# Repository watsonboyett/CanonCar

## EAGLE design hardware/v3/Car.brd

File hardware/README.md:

# Revision History

## v3A

- Added reverse polarity protection diode to power input (7V-35V input range?)

## Future Changes
* Change MCU to ATSAMD51J19A
  * Make it pin compatible with Metro M4 or Feather M4 boards, so Arduino IDE can be used easily
* Select better motor driver
  * TI DRV8848 - PWM interface, smaller, higher current output
  * Allegro A4970 - Same functionality as MTS62C19A, different pinout
  * Microchip MTS2916A - Same functionality as MTS62C19A, different pinout (same as A4970)
  * Toshiba TB6552 - Similar functionality as MTS62C19A
* Replace RFM12 module with RFM69 (RFM12 is obsolete now)
* Replace linear power regulators with buck converters
  * Is 5V supply actually needed?
  * Consider AOZ128x ICs
* Replace Mini-USB with Micro-USB connector
* Use SMT jack for DC plug (PJ-002AH-SMT)
* Use SMT headers for all external pin connectors
  * JST-PH connectors?
* Add support for battery charging circuit
  * NiMH on RC car side
  * LiPo on controller side

## Wiring Notes 

- all white lines connected to ground
- S-F (fire): orange, white
- S-R (right): purple, white
- S-L (left): green, white
- S-D (down): blue, white
- S-U (up): brown, white

- M3-F (fire): orange, red (red connected to +5V)
- M2-L/R (left/right): yellow, red
- M3-U/D (up/down): brown, red

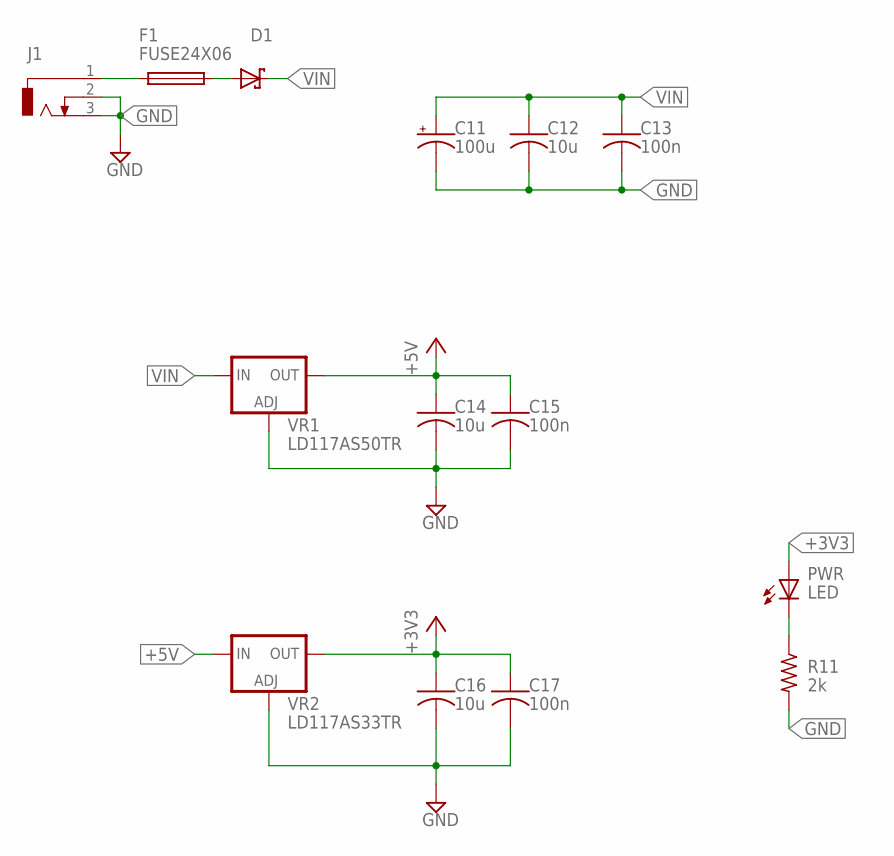
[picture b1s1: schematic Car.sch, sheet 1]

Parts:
C11: 100u; PANASONIC_C
C12, C14, C16: 10u; C1206
C13, C15, C17: 100n; C0805
D1: SCHOTTKY-DIODESMA; SMA
F1: FUSE24X06; 2SMD-24X06
J1: DCJ0303
PWR: LED; CHIP-LED0805
R11: 2k; R0805
VR1: LD117AS50TR; SOT223
VR2: LD117AS33TR; SOT223

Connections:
+3V3: C16.1, C17.1, PWR.A, VR2.2 (OUT), VR2.4 (OUT); also elsewhere on the board
+5V: C14.1, C15.1, VR1.2 (OUT), VR1.4 (OUT), VR2.3 (IN); also elsewhere on the board
GND: C11.-, C12.2, C13.2, C14.2, C15.2, C16.2, C17.2, J1.2, J1.3, R11.2, VR1.1 (ADJ), VR2.1 (ADJ); also elsewhere on the board
unnamed: D1.A, F1.P$2 (2)
unnamed: PWR.C, R11.1
VIN: C11.+, C12.1, C13.1, D1.C, VR1.3 (IN); also elsewhere on the board
VIN_PRF: F1.P$1 (1), J1.1

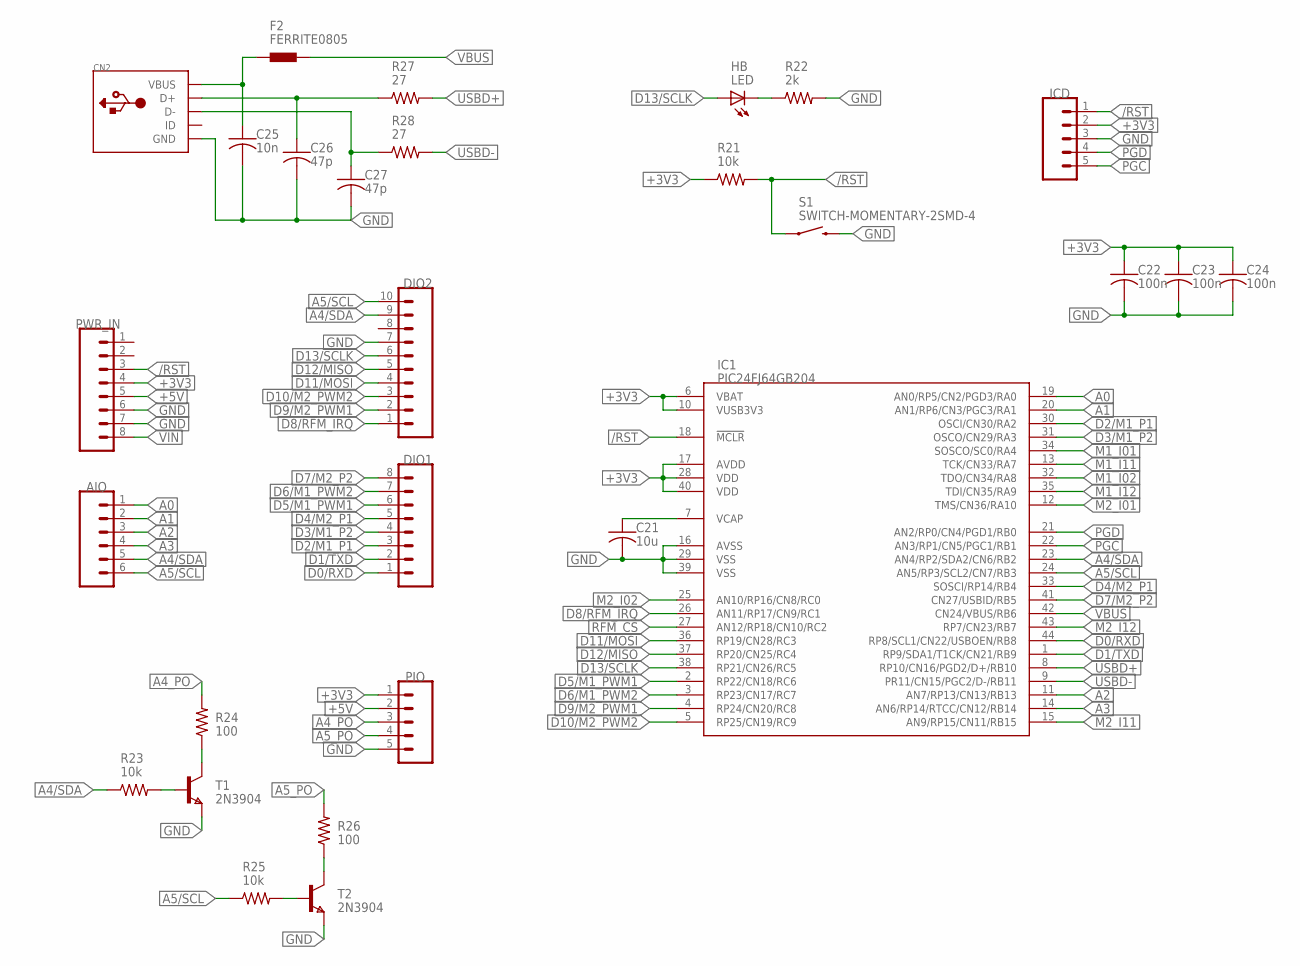
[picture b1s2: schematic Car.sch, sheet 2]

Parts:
AIO: M06LOCK; 1X06_LOCK
C21: 10u; C1206
C22, C23, C24: 100n; C0805
C25: 10n; C0805
C26, C27: 47p; C0805
CN2: USBMINIB; USB-MINIB
DIO1: M08LOCK; 1X08_LOCK
DIO2: M10LOCK; 1X10_LOCK
F2: FERRITE0805; 0805
HB: LED; CHIP-LED0805
IC1: PIC24FJ64GB204; TQFP44
ICD: M05LOCK; 1X05_LOCK
PIO: M05LOCK; 1X05_LOCK
PWR_IN: M08LOCK; 1X08_LOCK
R21, R23, R25: 10k; R0805
R22: 2k; R0805
R24, R26: 100; R0805
R27, R28: 27; R0805
S1: SWITCH-MOMENTARY-2SMD-4; TACTILE_SWITCH_TALL
T1, T2: 2N3904; SOT-23

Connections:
+3V3: C22.1, C23.1, C24.1, IC1.6 (VBAT), IC1.10 (VUSB3V3), IC1.17 (AVDD), IC1.28 (VDD), IC1.40 (VDD), ICD.2, PIO.1, PWR_IN.4, R21.1; also elsewhere on the board
+5V: PIO.2, PWR_IN.5; also elsewhere on the board
/RST: IC1.18 (!MCLR), ICD.1, PWR_IN.3, R21.2, S1.A2 (1); also elsewhere on the board
A0: AIO.1, IC1.19 (AN0/RP5/CN2/PGD3/RA0)
A1: AIO.2, IC1.20 (AN1/RP6/CN3/PGC3/RA1)
A2: AIO.3, IC1.11 (AN7/RP13/CN13/RB13)
A3: AIO.4, IC1.14 (AN6/RP14/RTCC/CN12/RB14)
A4/SDA: AIO.5, DIO2.9, IC1.23 (AN4/RP2/SDA2/CN6/RB2), R23.1
A4_PO: PIO.3, R24.2
A5/SCL: AIO.6, DIO2.10, IC1.24 (AN5/RP3/SCL2/CN7/RB3), R25.1
A5_PO: PIO.4, R26.2
D0/RXD: DIO1.1, IC1.44 (RP8/SCL1/CN22/USBOEN/RB8)
D1/TXD: DIO1.2, IC1.1 (RP9/SDA1/T1CK/CN21/RB9)
D2/M1_P1: DIO1.3, IC1.30 (OSCI/CN30/RA2); also elsewhere on the board
D3/M1_P2: DIO1.4, IC1.31 (OSCO/CN29/RA3); also elsewhere on the board
D4/M2_P1: DIO1.5, IC1.33 (SOSCI/RP14/RB4); also elsewhere on the board
D5/M1_PWM1: DIO1.6, IC1.2 (RP22/CN18/RC6); also elsewhere on the board
D6/M1_PWM2: DIO1.7, IC1.3 (RP23/CN17/RC7); also elsewhere on the board
D7/M2_P2: DIO1.8, IC1.41 (CN27/USBID/RB5); also elsewhere on the board
D8/RFM_IRQ: DIO2.1, IC1.26 (AN11/RP17/CN9/RC1); also elsewhere on the board
D9/M2_PWM1: DIO2.2, IC1.4 (RP24/CN20/RC8); also elsewhere on the board
D10/M2_PWM2: DIO2.3, IC1.5 (RP25/CN19/RC9); also elsewhere on the board
D11/MOSI: DIO2.4, IC1.36 (RP19/CN28/RC3); also elsewhere on the board
D12/MISO: DIO2.5, IC1.37 (RP20/CN25/RC4); also elsewhere on the board
D13/SCLK: DIO2.6, HB.A, IC1.38 (RP21/CN26/RC5); also elsewhere on the board
GND: C21.2, C22.2, C23.2, C24.2, C25.2, C26.2, C27.2, CN2.GND, DIO2.7, IC1.16 (AVSS), IC1.29 (VSS), IC1.39 (VSS), ICD.3, PIO.5, PWR_IN.6, PWR_IN.7, R22.2, S1.B2 (2), T1.2 (E), T2.2 (E); also elsewhere on the board
M1_I01: IC1.34 (SOSCO/SC0/RA4); also elsewhere on the board
M1_I02: IC1.32 (TDO/CN34/RA8); also elsewhere on the board
M1_I11: IC1.13 (TCK/CN33/RA7); also elsewhere on the board
M1_I12: IC1.35 (TDI/CN35/RA9); also elsewhere on the board
M2_I01: IC1.12 (TMS/CN36/RA10); also elsewhere on the board
M2_I02: IC1.25 (AN10/RP16/CN8/RC0); also elsewhere on the board
M2_I11: IC1.15 (AN9/RP15/CN11/RB15); also elsewhere on the board
M2_I12: IC1.43 (RP7/CN23/RB7); also elsewhere on the board
unnamed: R24.1, T1.1 (C)
unnamed: R26.1, T2.1 (C)
unnamed: R23.2, T1.3 (B)
unnamed: R25.2, T2.3 (B)
unnamed: C26.1, CN2.D+, R27.1
unnamed: C27.1, CN2.D-, R28.1
unnamed: C21.1, IC1.7 (VCAP)
unnamed: HB.C, R22.1
PGC: IC1.22 (AN3/RP1/CN5/PGC1/RB1), ICD.5
PGD: IC1.21 (AN2/RP0/CN4/PGD1/RB0), ICD.4
RFM_CS: IC1.27 (AN12/RP18/CN10/RC2); also elsewhere on the board
USBD+: IC1.8 (RP10/CN16/PGD2/D+/RB10), R27.2
USBD-: IC1.9 (PR11/CN15/PGC2/D-/RB11), R28.2
VBUS: F2.2, IC1.42 (CN24/VBUS/RB6)
VBUS-PRF: C25.1, CN2.VBUS, F2.1
VIN: PWR_IN.8; also elsewhere on the board

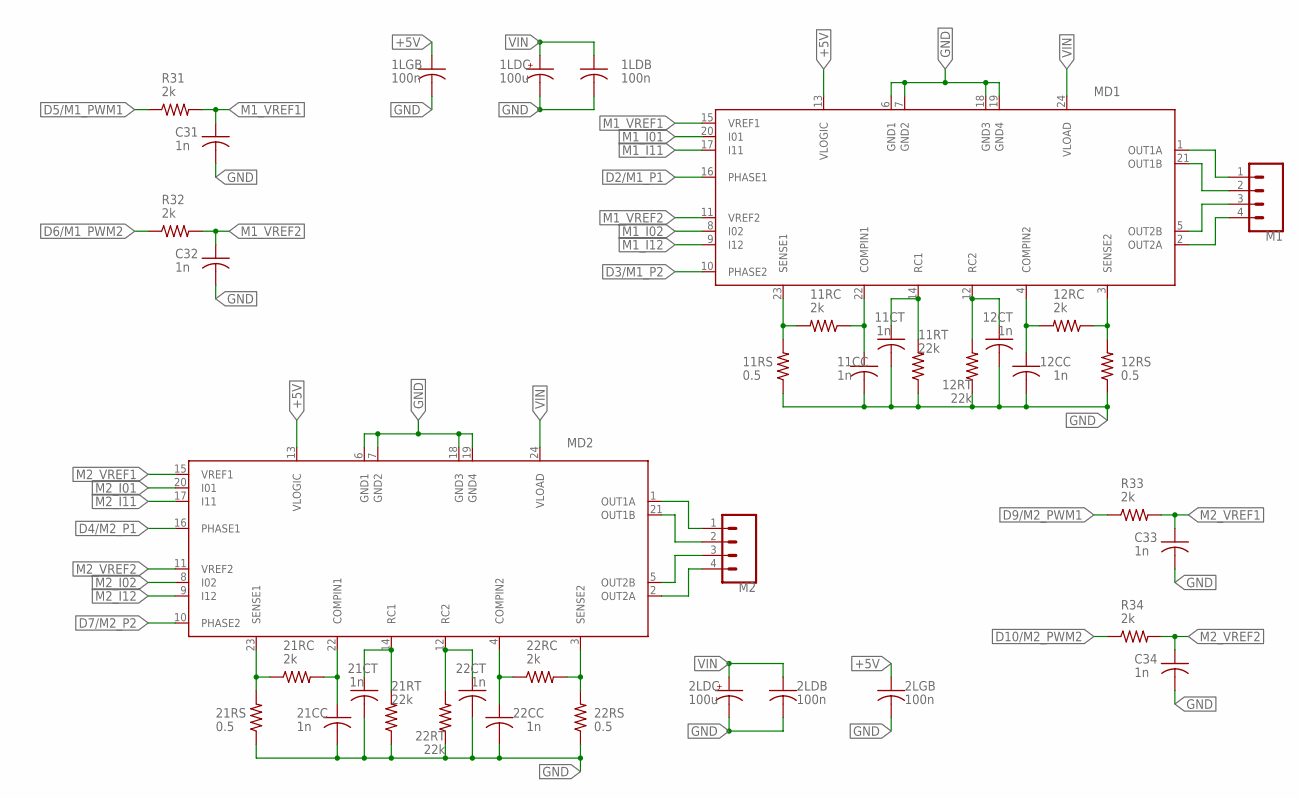
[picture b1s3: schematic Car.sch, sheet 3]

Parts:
1LDB, 1LGB, 2LDB, 2LGB: 100n; C0805
1LDC, 2LDC: 100u; PANASONIC_C
11CC, 11CT, 12CC, 12CT, 21CC, 21CT, 22CC, 22CT: 1n; C0805
11RC, 12RC, 21RC, 22RC: 2k; R0805
11RS, 12RS, 21RS, 22RS: 0.5; R1210
11RT, 12RT, 21RT, 22RT: 22k; R0805
C31, C32, C33, C34: 1n; C0805
M1, M2: M04LOCK; 1X04_LOCK
MD1, MD2: MTS62C19A; SOP24L
R31, R32, R33, R34: 2k; R0805

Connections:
+5V: 1LGB.1, 2LGB.1, MD1.13 (VLOGIC), MD2.13 (VLOGIC); also elsewhere on the board
D2/M1_P1: MD1.16 (PHASE1); also elsewhere on the board
D3/M1_P2: MD1.10 (PHASE2); also elsewhere on the board
D4/M2_P1: MD2.16 (PHASE1); also elsewhere on the board
D5/M1_PWM1: R31.1; also elsewhere on the board
D6/M1_PWM2: R32.1; also elsewhere on the board
D7/M2_P2: MD2.10 (PHASE2); also elsewhere on the board
D9/M2_PWM1: R33.1; also elsewhere on the board
D10/M2_PWM2: R34.1; also elsewhere on the board
GND: 1LDB.2, 1LDC.-, 1LGB.2, 2LDB.2, 2LDC.-, 2LGB.2, 11CC.2, 11CT.2, 11RS.1, 11RT.1, 12CC.2, 12CT.2, 12RS.1, 12RT.1, 21CC.2, 21CT.2, 21RS.1, 21RT.1, 22CC.2, 22CT.2, 22RS.1, 22RT.1, C31.2, C32.2, C33.2, C34.2, MD1.6 (GND1), MD1.7 (GND2), MD1.18 (GND3), MD1.19 (GND4), MD2.6 (GND1), MD2.7 (GND2), MD2.18 (GND3), MD2.19 (GND4); also elsewhere on the board
M1_I01: MD1.20 (I01); also elsewhere on the board
M1_I02: MD1.8 (I02); also elsewhere on the board
M1_I11: MD1.17 (I11); also elsewhere on the board
M1_I12: MD1.9 (I12); also elsewhere on the board
M1_VREF1: C31.1, MD1.15 (VREF1), R31.2
M1_VREF2: C32.1, MD1.11 (VREF2), R32.2
M2_I01: MD2.20 (I01); also elsewhere on the board
M2_I02: MD2.8 (I02); also elsewhere on the board
M2_I11: MD2.17 (I11); also elsewhere on the board
M2_I12: MD2.9 (I12); also elsewhere on the board
M2_VREF1: C33.1, MD2.15 (VREF1), R33.2
M2_VREF2: C34.1, MD2.11 (VREF2), R34.2
unnamed: M1.2, MD1.21 (OUT1B)
unnamed: M1.1, MD1.1 (OUT1A)
unnamed: M1.3, MD1.5 (OUT2B)
unnamed: M1.4, MD1.2 (OUT2A)
unnamed: M2.2, MD2.21 (OUT1B)
unnamed: M2.1, MD2.1 (OUT1A)
unnamed: M2.3, MD2.5 (OUT2B)
unnamed: M2.4, MD2.2 (OUT2A)
unnamed: 21RC.1, 21RS.2, MD2.23 (SENSE1)
unnamed: 21CC.1, 21RC.2, MD2.22 (COMPIN1)
unnamed: 22CT.1, 22RT.2, MD2.12 (RC2)
unnamed: 22RC.2, 22RS.2, MD2.3 (SENSE2)
unnamed: 22CC.1, 22RC.1, MD2.4 (COMPIN2)
unnamed: 21CT.1, 21RT.2, MD2.14 (RC1)
unnamed: 11RC.2, 11RS.2, MD1.23 (SENSE1)
unnamed: 11CC.1, 11RC.1, MD1.22 (COMPIN1)
unnamed: 12CC.1, 12RC.2, MD1.4 (COMPIN2)
unnamed: 12RC.1, 12RS.2, MD1.3 (SENSE2)
unnamed: 11CT.1, 11RT.2, MD1.14 (RC1)
unnamed: 12CT.1, 12RT.2, MD1.12 (RC2)
VIN: 1LDB.1, 1LDC.+, 2LDB.1, 2LDC.+, MD1.24 (VLOAD), MD2.24 (VLOAD); also elsewhere on the board

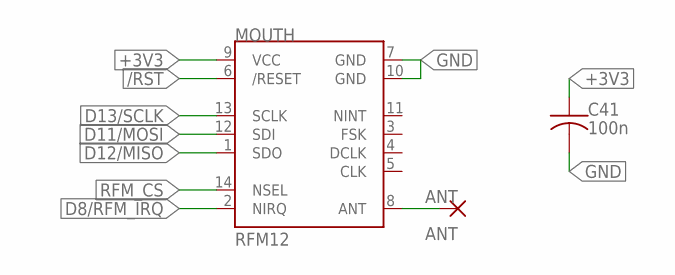
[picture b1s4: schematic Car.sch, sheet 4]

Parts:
ANT: ANT; 2,15/1,0
C41: 100n; C0805
MOUTH: RFM12; RFM12-XXX-S2

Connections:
+3V3: C41.1, MOUTH.9 (VCC); also elsewhere on the board
GND: C41.2, MOUTH.7 (GND), MOUTH.10 (GND); also elsewhere on the board
unnamed 48: ANT.1, MOUTH.8 (ANT); also elsewhere on the board

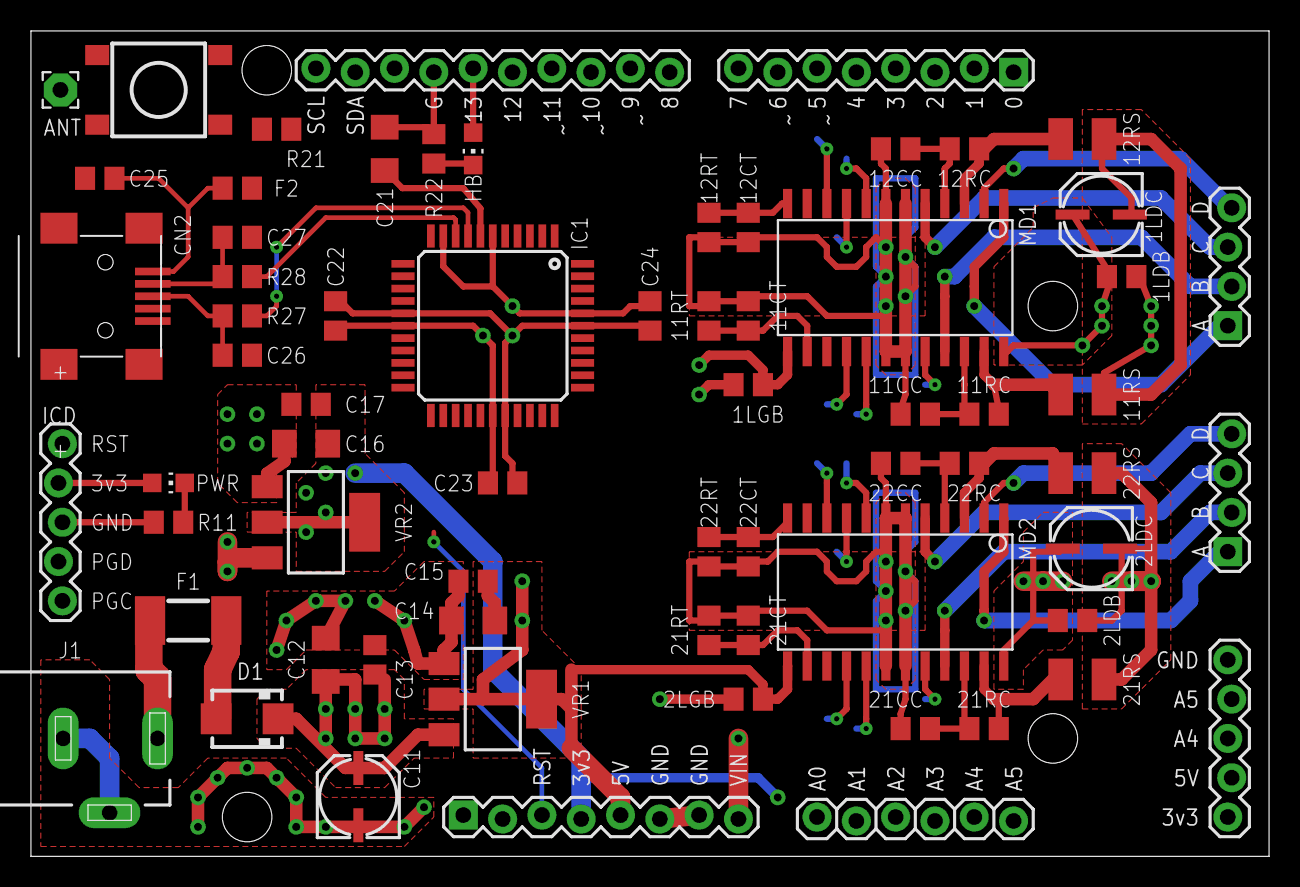
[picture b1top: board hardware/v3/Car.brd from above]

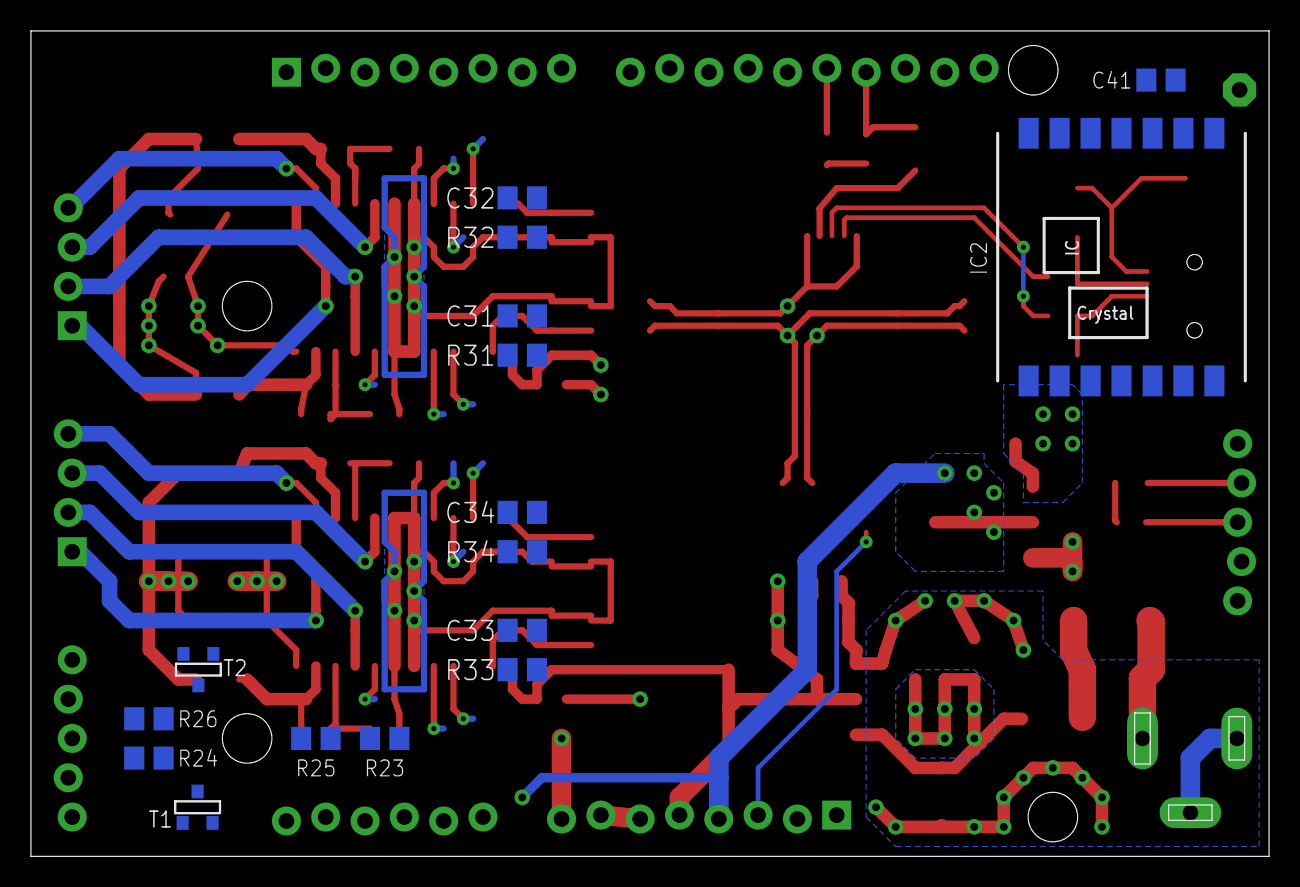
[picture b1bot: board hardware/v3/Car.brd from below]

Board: 4 copper layers, 80.0 x 53.3 mm, 83 parts (16 on the bottom side), 78 nets.

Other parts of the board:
IC2: RFM12; RFM12-XXX-S2

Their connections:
+3V3: IC2.9; also elsewhere on the board
/RST: IC2.6; also elsewhere on the board
D8/RFM_IRQ: IC2.2; also elsewhere on the board
D11/MOSI: IC2.12; also elsewhere on the board
D12/MISO: IC2.1; also elsewhere on the board
D13/SCLK: IC2.13; also elsewhere on the board
GND: IC2.7, IC2.10; also elsewhere on the board
unnamed 48: IC2.8; also elsewhere on the board
RFM_CS: IC2.14; also elsewhere on the board

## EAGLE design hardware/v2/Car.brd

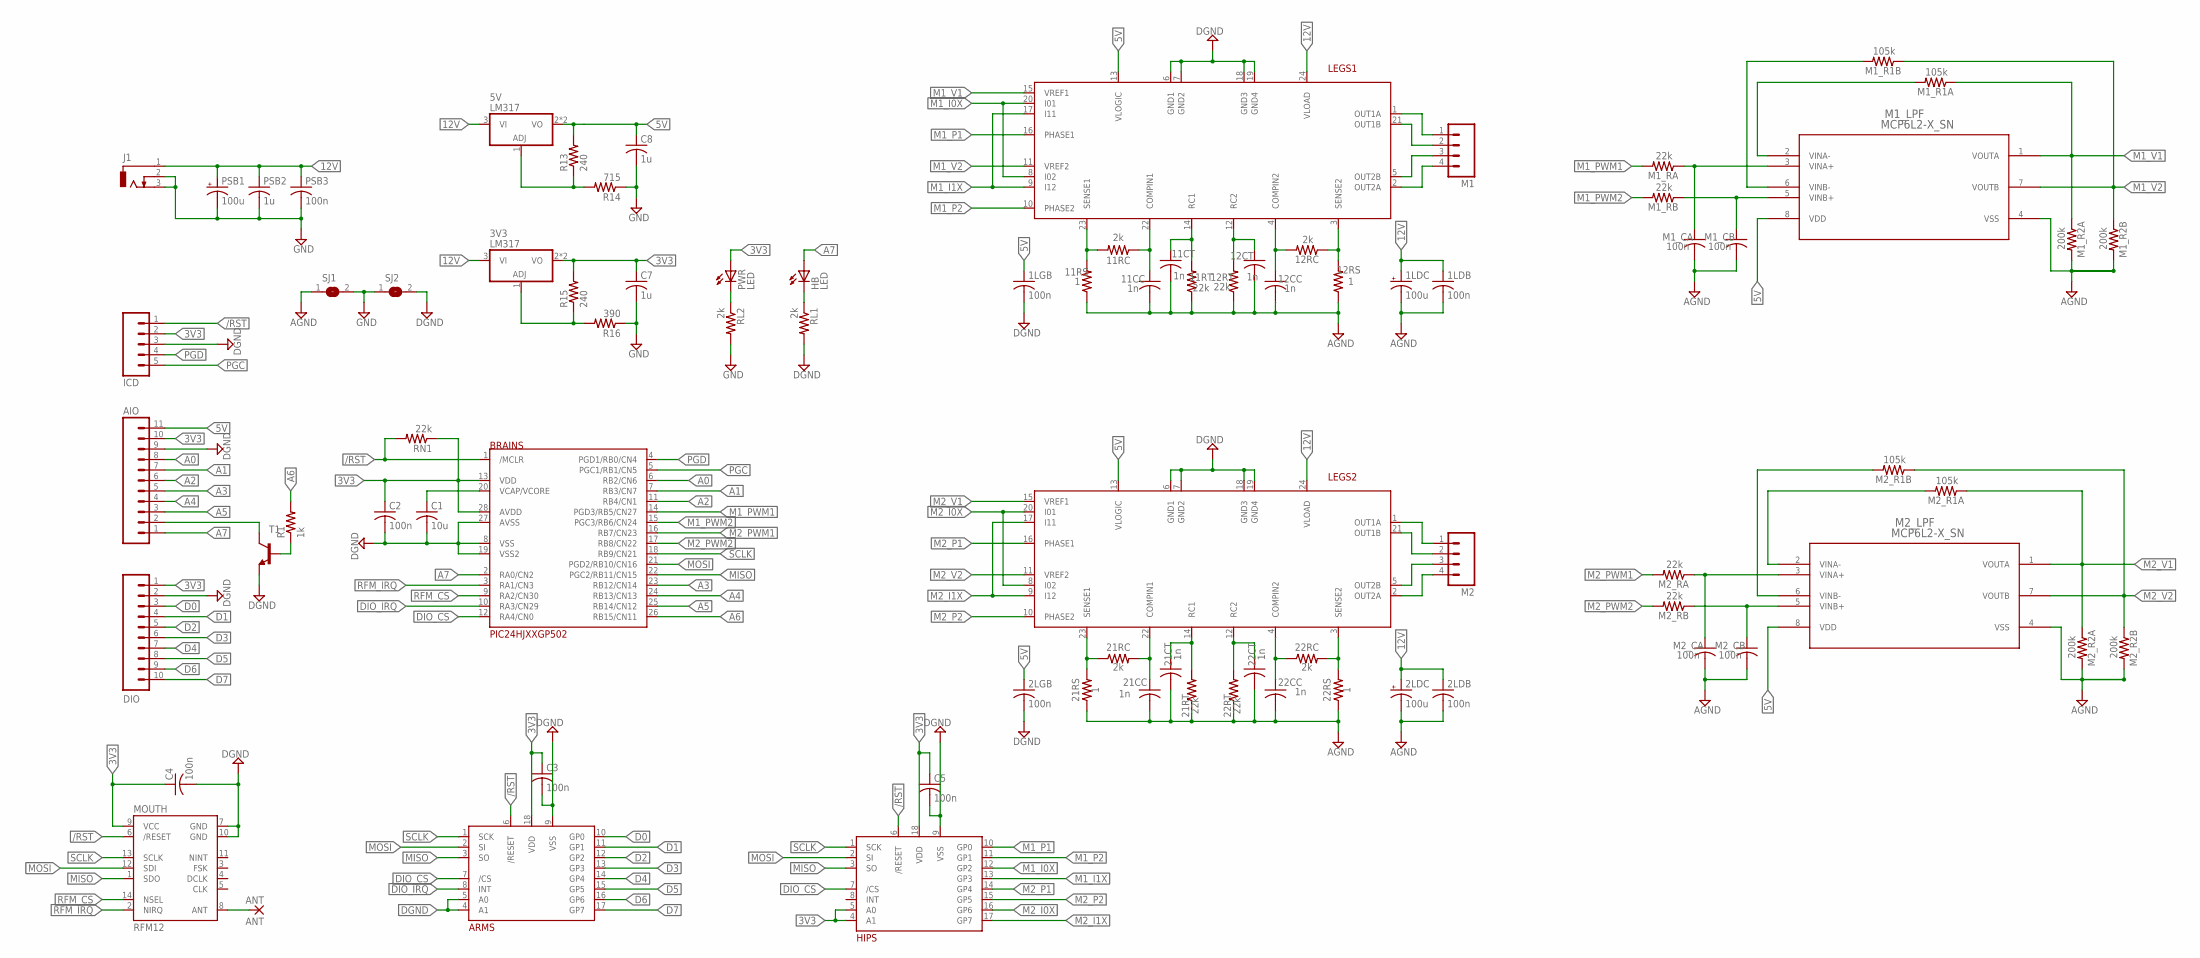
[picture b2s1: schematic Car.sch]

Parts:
1LDB, 1LGB, 2LDB, 2LGB: 100n; C0805
1LDC, 2LDC: 100u; PANASONIC_C
3V3, 5V: LM317; SOT23
11CC, 11CT, 12CC, 12CT, 21CC, 21CT, 22CC, 22CT: 1n; C0805
11RC, 12RC, 21RC, 22RC: 2k; R0805
11RS, 12RS, 21RS, 22RS: 1; R2512
11RT, 12RT, 21RT, 22RT: 22k; R0805
AIO: M11LOCK; 1X11_LOCK
ANT: ANT; 2,15/1,0
ARMS: MCP23S08; SO-18W
BRAINS: PIC24HJXXGP502; SO28W
C1: 10u; C1206
C2, C3, C4, C5: 100n; C0805
C7, C8: 1u; C1206
DIO: M10LOCK; 1X10_LOCK
HB: LED; CHIP-LED0805
HIPS: MCP23S08; SO-18W
ICD: M05LOCK; 1X05_LOCK
J1: DCJ0303
LEGS1, LEGS2: MTS62C19A; SOP24L
M1, M2: M04LOCK_LONGPADS; 1X04_LOCK_LONGPADS
M1_CA, M1_CB, M2_CA, M2_CB: 100n; C0805
M1_LPF, M2_LPF: MCP6L2-X_SN; SOIC8-N_MC
M1_R1A, M1_R1B, M2_R1A, M2_R1B: 105k; R0805
M1_R2A, M1_R2B, M2_R2A, M2_R2B: 200k; R0805
M1_RA, M1_RB, M2_RA, M2_RB: 22k; R0805
MOUTH: RFM12; RFM12-XXX-S2
PSB1: 100u; PANASONIC_C
PSB2: 1u; C1206
PSB3: 100n; C0805
PWR: LED; CHIP-LED0805
R1: 1k; R0805
R13, R15: 240; R0805
R14: 715; R0805
R16: 390; R0805
RL1, RL2: 2k; R0805
RN1: 22k; R0805
SJ1, SJ2: SJ
T1: BC817-16-NPN-SOT23-BEC; SOT23-BEC

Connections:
3V3: 3V3.2 (VO), 3V3.4 (VO), AIO.10, ARMS.18 (VDD), BRAINS.13 (VDD), BRAINS.28 (AVDD), C2.1, C3.1, C4.1, C5.1, C7.1, DIO.1, HIPS.4 (A1), HIPS.5 (A0), HIPS.18 (VDD), ICD.2, MOUTH.9 (VCC), PWR.A, R15.2, RN1.1
5V: 1LGB.1, 2LGB.1, 5V.2 (VO), 5V.4 (VO), AIO.11, C8.1, LEGS1.13 (VLOGIC), LEGS2.13 (VLOGIC), M1_LPF.8 (VDD), M2_LPF.8 (VDD), R13.2
12V: 1LDB.1, 1LDC.+, 2LDB.1, 2LDC.+, 3V3.3 (VI), 5V.3 (VI), J1.1, LEGS1.24 (VLOAD), LEGS2.24 (VLOAD), PSB1.+, PSB2.1, PSB3.1
/RST: ARMS.6 (/RESET), BRAINS.1 (/MCLR), HIPS.6 (/RESET), ICD.1, MOUTH.6 (/RESET), RN1.2
A0: AIO.8, BRAINS.6 (RB2/CN6)
A1: AIO.7, BRAINS.7 (RB3/CN7)
A2: AIO.6, BRAINS.11 (RB4/CN1)
A3: AIO.5, BRAINS.23 (RB12/CN14)
A4: AIO.4, BRAINS.24 (RB13/CN13)
A5: AIO.3, BRAINS.25 (RB14/CN12)
A6: BRAINS.26 (RB15/CN11), R1.2
A7: AIO.1, BRAINS.2 (RA0/CN2), HB.A
AGND: 1LDB.2, 1LDC.-, 2LDB.2, 2LDC.-, 11CC.2, 11CT.2, 11RS.1, 11RT.1, 12CC.2, 12CT.2, 12RS.1, 12RT.1, 21CC.2, 21CT.2, 21RS.1, 21RT.1, 22CC.2, 22CT.2, 22RS.1, 22RT.1, M1_CA.2, M1_CB.2, M1_LPF.4 (VSS), M1_R2A.2, M1_R2B.2, M2_CA.2, M2_CB.2, M2_LPF.4 (VSS), M2_R2A.2, M2_R2B.2, SJ1.1
D0: ARMS.10 (GP0), DIO.3
D1: ARMS.11 (GP1), DIO.4
D2: ARMS.12 (GP2), DIO.5
D3: ARMS.13 (GP3), DIO.6
D4: ARMS.14 (GP4), DIO.7
D5: ARMS.15 (GP5), DIO.8
D6: ARMS.16 (GP6), DIO.9
D7: ARMS.17 (GP7), DIO.10
DGND: 1LGB.2, 2LGB.2, AIO.9, ARMS.4 (A1), ARMS.5 (A0), ARMS.9 (VSS), BRAINS.8 (VSS), BRAINS.19 (VSS2), BRAINS.27 (AVSS), C1.2, C2.2, C3.2, C4.2, C5.2, DIO.2, HIPS.9 (VSS), ICD.3, LEGS1.6 (GND1), LEGS1.7 (GND2), LEGS1.18 (GND3), LEGS1.19 (GND4), LEGS2.6 (GND1), LEGS2.7 (GND2), LEGS2.18 (GND3), LEGS2.19 (GND4), MOUTH.7 (GND), MOUTH.10 (GND), RL1.2, SJ2.2, T1.E
DIO_CS: ARMS.7 (/CS), BRAINS.12 (RA4/CN0), HIPS.7 (/CS)
DIO_IRQ: ARMS.8 (INT), BRAINS.10 (RA3/CN29)
GND: C7.2, C8.2, J1.2, J1.3, PSB1.-, PSB2.2, PSB3.2, R14.1, R16.1, RL2.2, SJ1.2, SJ2.1
M1_I0X: HIPS.12 (GP2), LEGS1.8 (I02), LEGS1.20 (I01)
M1_I1X: HIPS.13 (GP3), LEGS1.9 (I12), LEGS1.17 (I11)
M1_P1: HIPS.10 (GP0), LEGS1.16 (PHASE1)
M1_P2: HIPS.11 (GP1), LEGS1.10 (PHASE2)
M1_PWM1: BRAINS.14 (PGD3/RB5/CN27), M1_RA.2
M1_PWM2: BRAINS.15 (PGC3/RB6/CN24), M1_RB.2
M1_V1: LEGS1.15 (VREF1), M1_LPF.1 (VOUTA), M1_R1A.1, M1_R2A.1
M1_V2: LEGS1.11 (VREF2), M1_LPF.7 (VOUTB), M1_R1B.1, M1_R2B.1
M2_I0X: HIPS.16 (GP6), LEGS2.8 (I02), LEGS2.20 (I01)
M2_I1X: HIPS.17 (GP7), LEGS2.9 (I12), LEGS2.17 (I11)
M2_P1: HIPS.14 (GP4), LEGS2.16 (PHASE1)
M2_P2: HIPS.15 (GP5), LEGS2.10 (PHASE2)
M2_PWM1: BRAINS.16 (RB7/CN23), M2_RA.2
M2_PWM2: BRAINS.17 (RB8/CN22), M2_RB.2
M2_V1: LEGS2.15 (VREF1), M2_LPF.1 (VOUTA), M2_R1A.1, M2_R2A.1
M2_V2: LEGS2.11 (VREF2), M2_LPF.7 (VOUTB), M2_R1B.1, M2_R2B.1
MISO: ARMS.3 (SO), BRAINS.22 (PGC2/RB11/CN15), HIPS.3 (SO), MOUTH.1 (SDO)
MOSI: ARMS.2 (SI), BRAINS.21 (PGD2/RB10/CN16), HIPS.2 (SI), MOUTH.12 (SDI)
unnamed: LEGS1.21 (OUT1B), M1.2
unnamed: LEGS1.1 (OUT1A), M1.1
unnamed: M1_CA.1, M1_LPF.3 (VINA+), M1_RA.1
unnamed: LEGS1.5 (OUT2B), M1.3
unnamed: LEGS1.2 (OUT2A), M1.4
unnamed: LEGS2.21 (OUT1B), M2.2
unnamed: M1_LPF.2 (VINA-), M1_R1A.2
unnamed: LEGS2.1 (OUT1A), M2.1
unnamed: LEGS2.5 (OUT2B), M2.3
unnamed: LEGS2.2 (OUT2A), M2.4
unnamed: ANT.1, MOUTH.8 (ANT)
unnamed: M2_CA.1, M2_LPF.3 (VINA+), M2_RA.1
unnamed: 21RC.1, 21RS.2, LEGS2.23 (SENSE1)
unnamed: 21CC.1, 21RC.2, LEGS2.22 (COMPIN1)
unnamed: 22CT.1, 22RT.2, LEGS2.12 (RC2)
unnamed: 22RC.2, 22RS.2, LEGS2.3 (SENSE2)
unnamed: 22CC.1, 22RC.1, LEGS2.4 (COMPIN2)
unnamed: 21CT.1, 21RT.2, LEGS2.14 (RC1)
unnamed: M2_LPF.2 (VINA-), M2_R1A.2
unnamed: 3V3.1 (ADJ), R15.1, R16.2
unnamed: M1_LPF.6 (VINB-), M1_R1B.2
unnamed: M1_CB.1, M1_LPF.5 (VINB+), M1_RB.1
unnamed: M2_LPF.6 (VINB-), M2_R1B.2
unnamed: M2_CB.1, M2_LPF.5 (VINB+), M2_RB.1
unnamed: AIO.2, T1.C
unnamed: 5V.1 (ADJ), R13.1, R14.2
unnamed: R1.1, T1.B
unnamed: 11RC.2, 11RS.2, LEGS1.23 (SENSE1)
unnamed: 11CC.1, 11RC.1, LEGS1.22 (COMPIN1)
unnamed: 12CC.1, 12RC.2, LEGS1.4 (COMPIN2)
unnamed: 12RC.1, 12RS.2, LEGS1.3 (SENSE2)
unnamed: BRAINS.20 (VCAP/VCORE), C1.1
unnamed: 11CT.1, 11RT.2, LEGS1.14 (RC1)
unnamed: 12CT.1, 12RT.2, LEGS1.12 (RC2)
unnamed: HB.C, RL1.1
unnamed: PWR.C, RL2.1
PGC: BRAINS.5 (PGC1/RB1/CN5), ICD.5
PGD: BRAINS.4 (PGD1/RB0/CN4), ICD.4
RFM_CS: BRAINS.9 (RA2/CN30), MOUTH.14 (NSEL)
RFM_IRQ: BRAINS.3 (RA1/CN3), MOUTH.2 (NIRQ)
SCLK: ARMS.1 (SCK), BRAINS.18 (RB9/CN21), HIPS.1 (SCK), MOUTH.13 (SCLK)

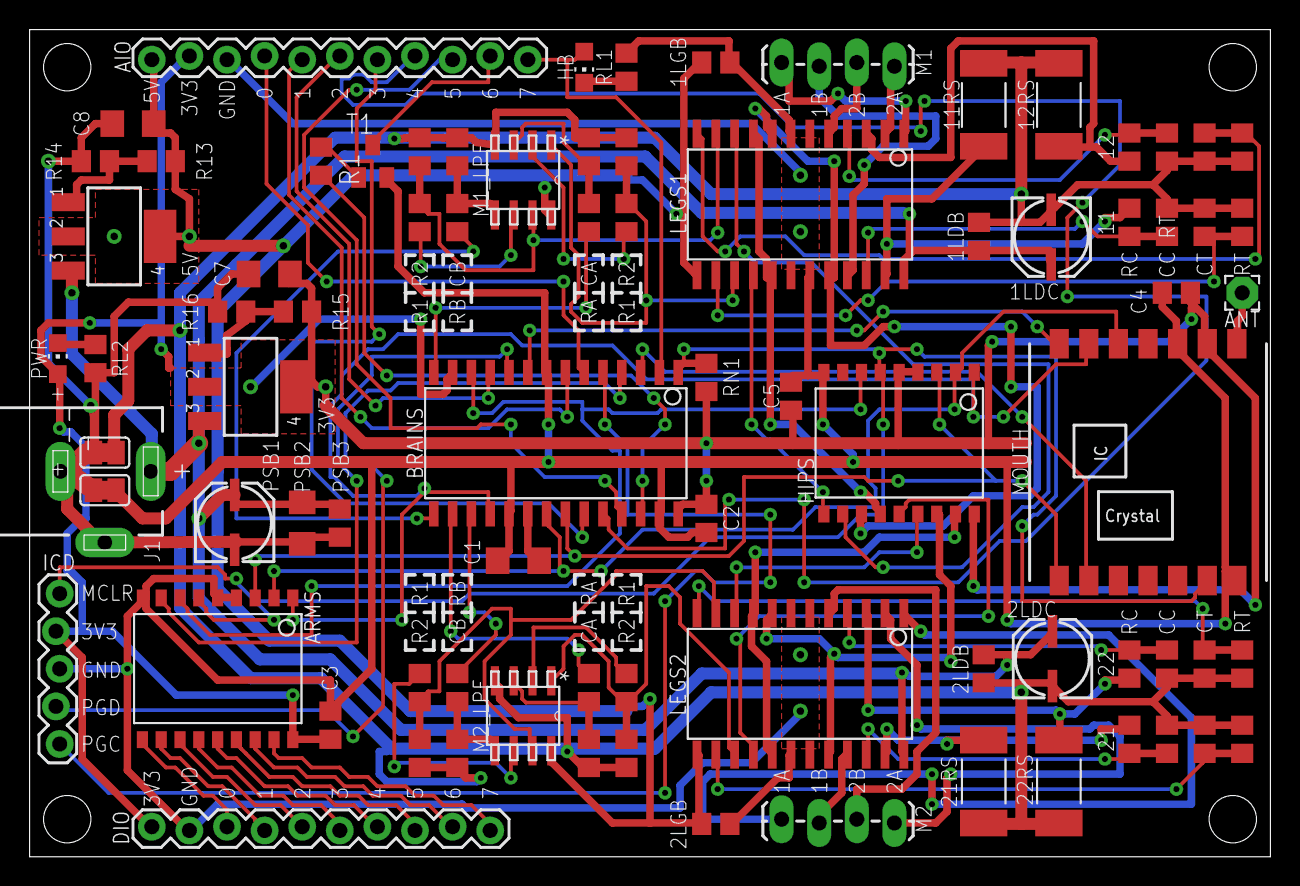
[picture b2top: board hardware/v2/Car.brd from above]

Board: 2 copper layers, 83.8 x 55.9 mm, 82 parts (0 on the bottom side), 84 nets.

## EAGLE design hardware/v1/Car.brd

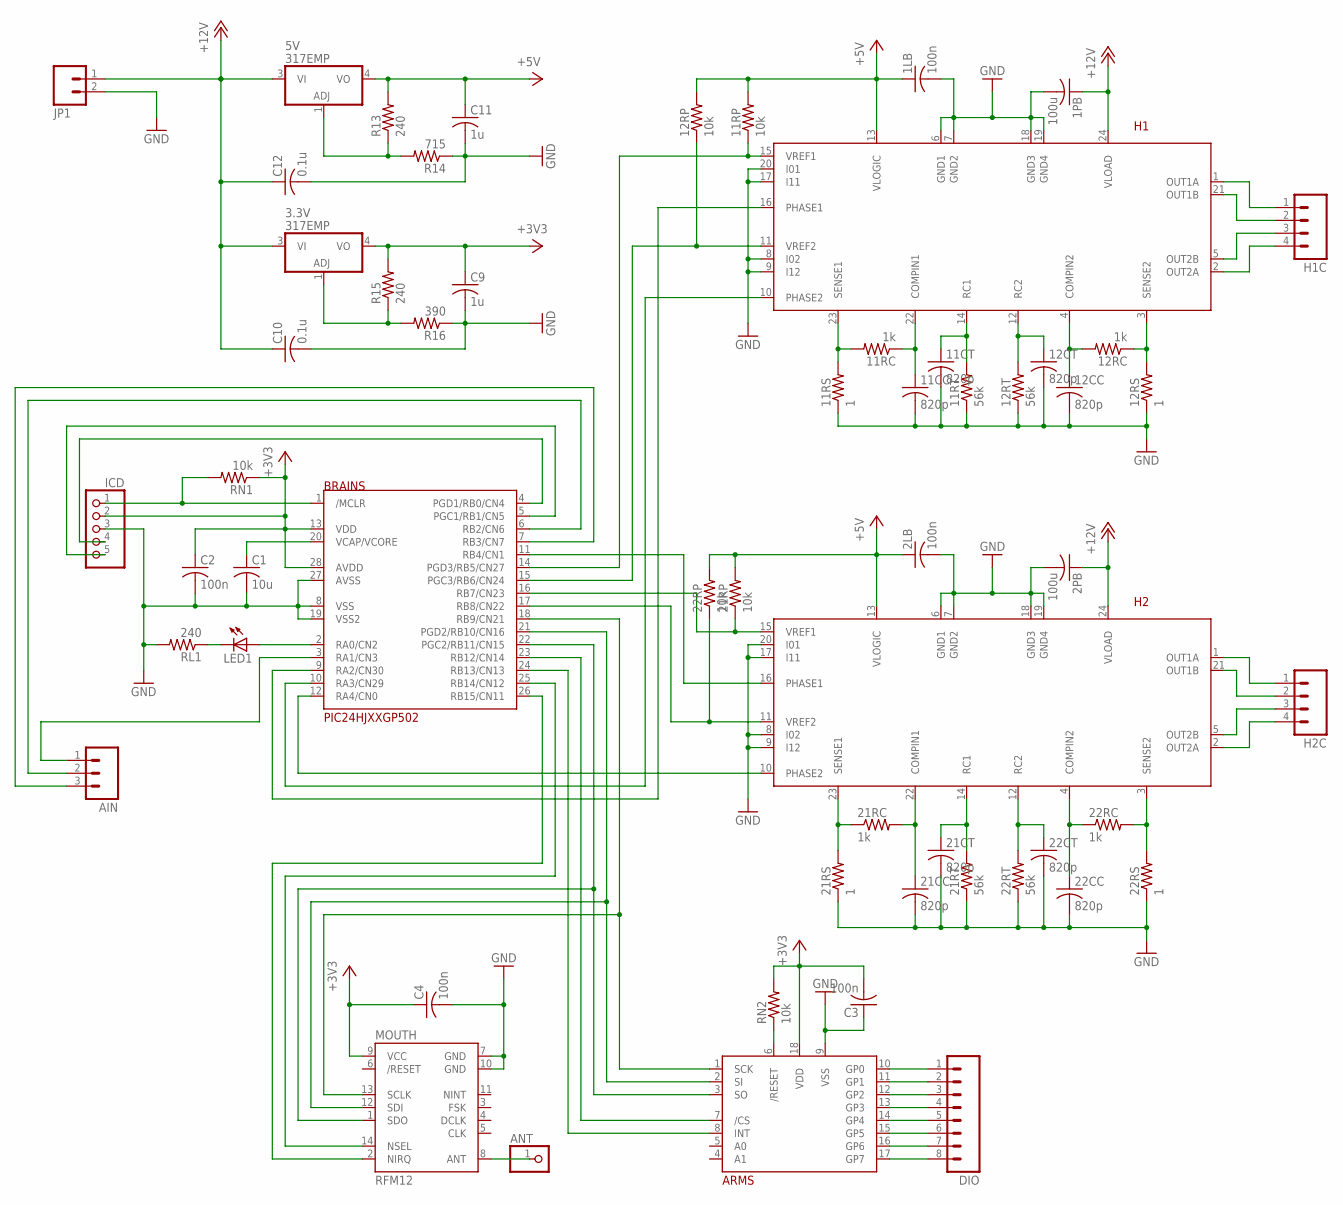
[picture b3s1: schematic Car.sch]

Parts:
1LB, 2LB: 100n; C0805
1PB, 2PB: 100u; C0805
3.3V, 5V: 317EMP; SOT223
11CC, 11CT, 12CC, 12CT, 21CC, 21CT, 22CC, 22CT: 820p; C0805
11RC, 12RC, 21RC, 22RC: 1k; R0805
11RP, 12RP, 21RP, 22RP: 10k; R0805
11RS, 12RS, 21RS, 22RS: 1; R2512
11RT, 12RT, 21RT, 22RT: 56k; R0805
AIN: M03POLAR; MOLEX-1X3
ANT: PINHD-1X1; 1X01
ARMS: MCP23S08; SO-18W
BRAINS: PIC24HJXXGP502; SO28W
C1: 10u; C0805
C2, C3, C4: 100n; C0805
C9, C11: 1u; C0805
C10, C12: 0.1u; C0805
DIO: M081X08; 1X08
H1, H2: MTS62C19A; SOP24L
H1C, H2C: M04POLAR; MOLEX-1X4
ICD: PINHD-1X5; 1X05
JP1: M02POLAR; MOLEX-1X2
LED1: LEDCHIP-LED0805; CHIP-LED0805
MOUTH: RFM12; RFM12-XXX-S2
R13, R15: 240; R0805
R14: 715; R0805
R16: 390; R0805
RL1: 240; R0805
RN1, RN2: 10k; R0805

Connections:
+3V3: 3.3V.4 (VO), ARMS.18 (VDD), BRAINS.13 (VDD), BRAINS.28 (AVDD), C2.1, C3.2, C4.1, C9.1, ICD.2, MOUTH.9 (VCC), R15.2, RN1.1, RN2.2
+5V: 1LB.1, 2LB.1, 5V.4 (VO), 11RP.2, 12RP.2, 21RP.2, 22RP.2, C11.1, H1.13 (VLOGIC), H2.13 (VLOGIC), R13.2
+12V: 1PB.1, 2PB.1, 3.3V.3 (VI), 5V.3 (VI), C10.1, C12.1, H1.24 (VLOAD), H2.24 (VLOAD), JP1.1
GND: 1LB.2, 1PB.2, 2LB.2, 2PB.2, 11CC.2, 11CT.2, 11RS.1, 11RT.1, 12CC.2, 12CT.2, 12RS.1, 12RT.1, 21CC.2, 21CT.2, 21RS.1, 21RT.1, 22CC.2, 22CT.2, 22RS.1, 22RT.1, ARMS.9 (VSS), BRAINS.8 (VSS), BRAINS.19 (VSS2), BRAINS.27 (AVSS), C1.2, C2.2, C3.1, C4.2, C9.2, C10.2, C11.2, C12.2, H1.6 (GND1), H1.7 (GND2), H1.8 (I02), H1.9 (I12), H1.17 (I11), H1.18 (GND3), H1.19 (GND4), H1.20 (I01), H2.6 (GND1), H2.7 (GND2), H2.8 (I02), H2.9 (I12), H2.17 (I11), H2.18 (GND3), H2.19 (GND4), H2.20 (I01), ICD.3, JP1.2, MOUTH.7 (GND), MOUTH.10 (GND), R14.1, R16.1, RL1.2
unnamed: H1.21 (OUT1B), H1C.2
unnamed: H1.1 (OUT1A), H1C.1
unnamed: BRAINS.4 (PGD1/RB0/CN4), ICD.4
unnamed: H1.5 (OUT2B), H1C.3
unnamed: H1.2 (OUT2A), H1C.4
unnamed: H2.21 (OUT1B), H2C.2
unnamed: ARMS.1 (SCK), BRAINS.18 (RB9/CN21), MOUTH.13 (SCLK)
unnamed: H2.1 (OUT1A), H2C.1
unnamed: H2.5 (OUT2B), H2C.3
unnamed: H2.2 (OUT2A), H2C.4
unnamed: BRAINS.1 (/MCLR), ICD.1, RN1.2
unnamed: ARMS.16 (GP6), DIO.7
unnamed: 21RC.1, 21RS.2, H2.23 (SENSE1)
unnamed: 21CC.1, 21RC.2, H2.22 (COMPIN1)
unnamed: 22CT.1, 22RT.2, H2.12 (RC2)
unnamed: 22RC.2, 22RS.2, H2.3 (SENSE2)
unnamed: 22CC.1, 22RC.1, H2.4 (COMPIN2)
unnamed: 21CT.1, 21RT.2, H2.14 (RC1)
unnamed: 22RP.1, BRAINS.17 (RB8/CN22), H2.11 (VREF2)
unnamed: 3.3V.1 (ADJ), R15.1, R16.2
unnamed: 12RP.1, BRAINS.15 (PGC3/RB6/CN24), H1.11 (VREF2)
unnamed: BRAINS.25 (RB14/CN12), MOUTH.14 (NSEL)
unnamed: BRAINS.11 (RB4/CN1), H2.16 (PHASE1)
unnamed: BRAINS.26 (RB15/CN11), MOUTH.2 (NIRQ)
unnamed: ARMS.2 (SI), BRAINS.21 (PGD2/RB10/CN16), MOUTH.12 (SDI)
unnamed: ARMS.3 (SO), BRAINS.22 (PGC2/RB11/CN15), MOUTH.1 (SDO)
unnamed: 5V.1 (ADJ), R13.1, R14.2
unnamed: BRAINS.5 (PGC1/RB1/CN5), ICD.5
unnamed: BRAINS.9 (RA2/CN30), H1.16 (PHASE1)
unnamed: 11RP.1, BRAINS.14 (PGD3/RB5/CN27), H1.15 (VREF1)
unnamed: 11RC.2, 11RS.2, H1.23 (SENSE1)
unnamed: BRAINS.10 (RA3/CN29), H1.10 (PHASE2)
unnamed: 11CC.1, 11RC.1, H1.22 (COMPIN1)
unnamed: 12CC.1, 12RC.2, H1.4 (COMPIN2)
unnamed: 12RC.1, 12RS.2, H1.3 (SENSE2)
unnamed: ARMS.7 (/CS), BRAINS.23 (RB12/CN14)
unnamed: ARMS.8 (INT), BRAINS.24 (RB13/CN13)
unnamed: 21RP.1, BRAINS.16 (RB7/CN23), H2.15 (VREF1)
unnamed: ANT.1, MOUTH.8 (ANT)
unnamed: BRAINS.20 (VCAP/VCORE), C1.1
unnamed: 11CT.1, 11RT.2, H1.14 (RC1)
unnamed: 12CT.1, 12RT.2, H1.12 (RC2)
unnamed: ARMS.10 (GP0), DIO.1
unnamed: ARMS.11 (GP1), DIO.2
unnamed: BRAINS.2 (RA0/CN2), LED1.A
unnamed: LED1.C, RL1.1
unnamed: BRAINS.12 (RA4/CN0), H2.10 (PHASE2)
unnamed: ARMS.12 (GP2), DIO.3
unnamed: ARMS.13 (GP3), DIO.4
unnamed: ARMS.14 (GP4), DIO.5
unnamed: ARMS.15 (GP5), DIO.6
unnamed: ARMS.17 (GP7), DIO.8
unnamed: AIN.1, BRAINS.3 (RA1/CN3)
unnamed: AIN.2, BRAINS.6 (RB2/CN6)
unnamed: AIN.3, BRAINS.7 (RB3/CN7)
unnamed: ARMS.6 (/RESET), RN2.1

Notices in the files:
parts and their libraries:
SparkFun-RF: Licensing: CC v3.0 Share-Alike You are welcome to use this library for commercial purposes.
